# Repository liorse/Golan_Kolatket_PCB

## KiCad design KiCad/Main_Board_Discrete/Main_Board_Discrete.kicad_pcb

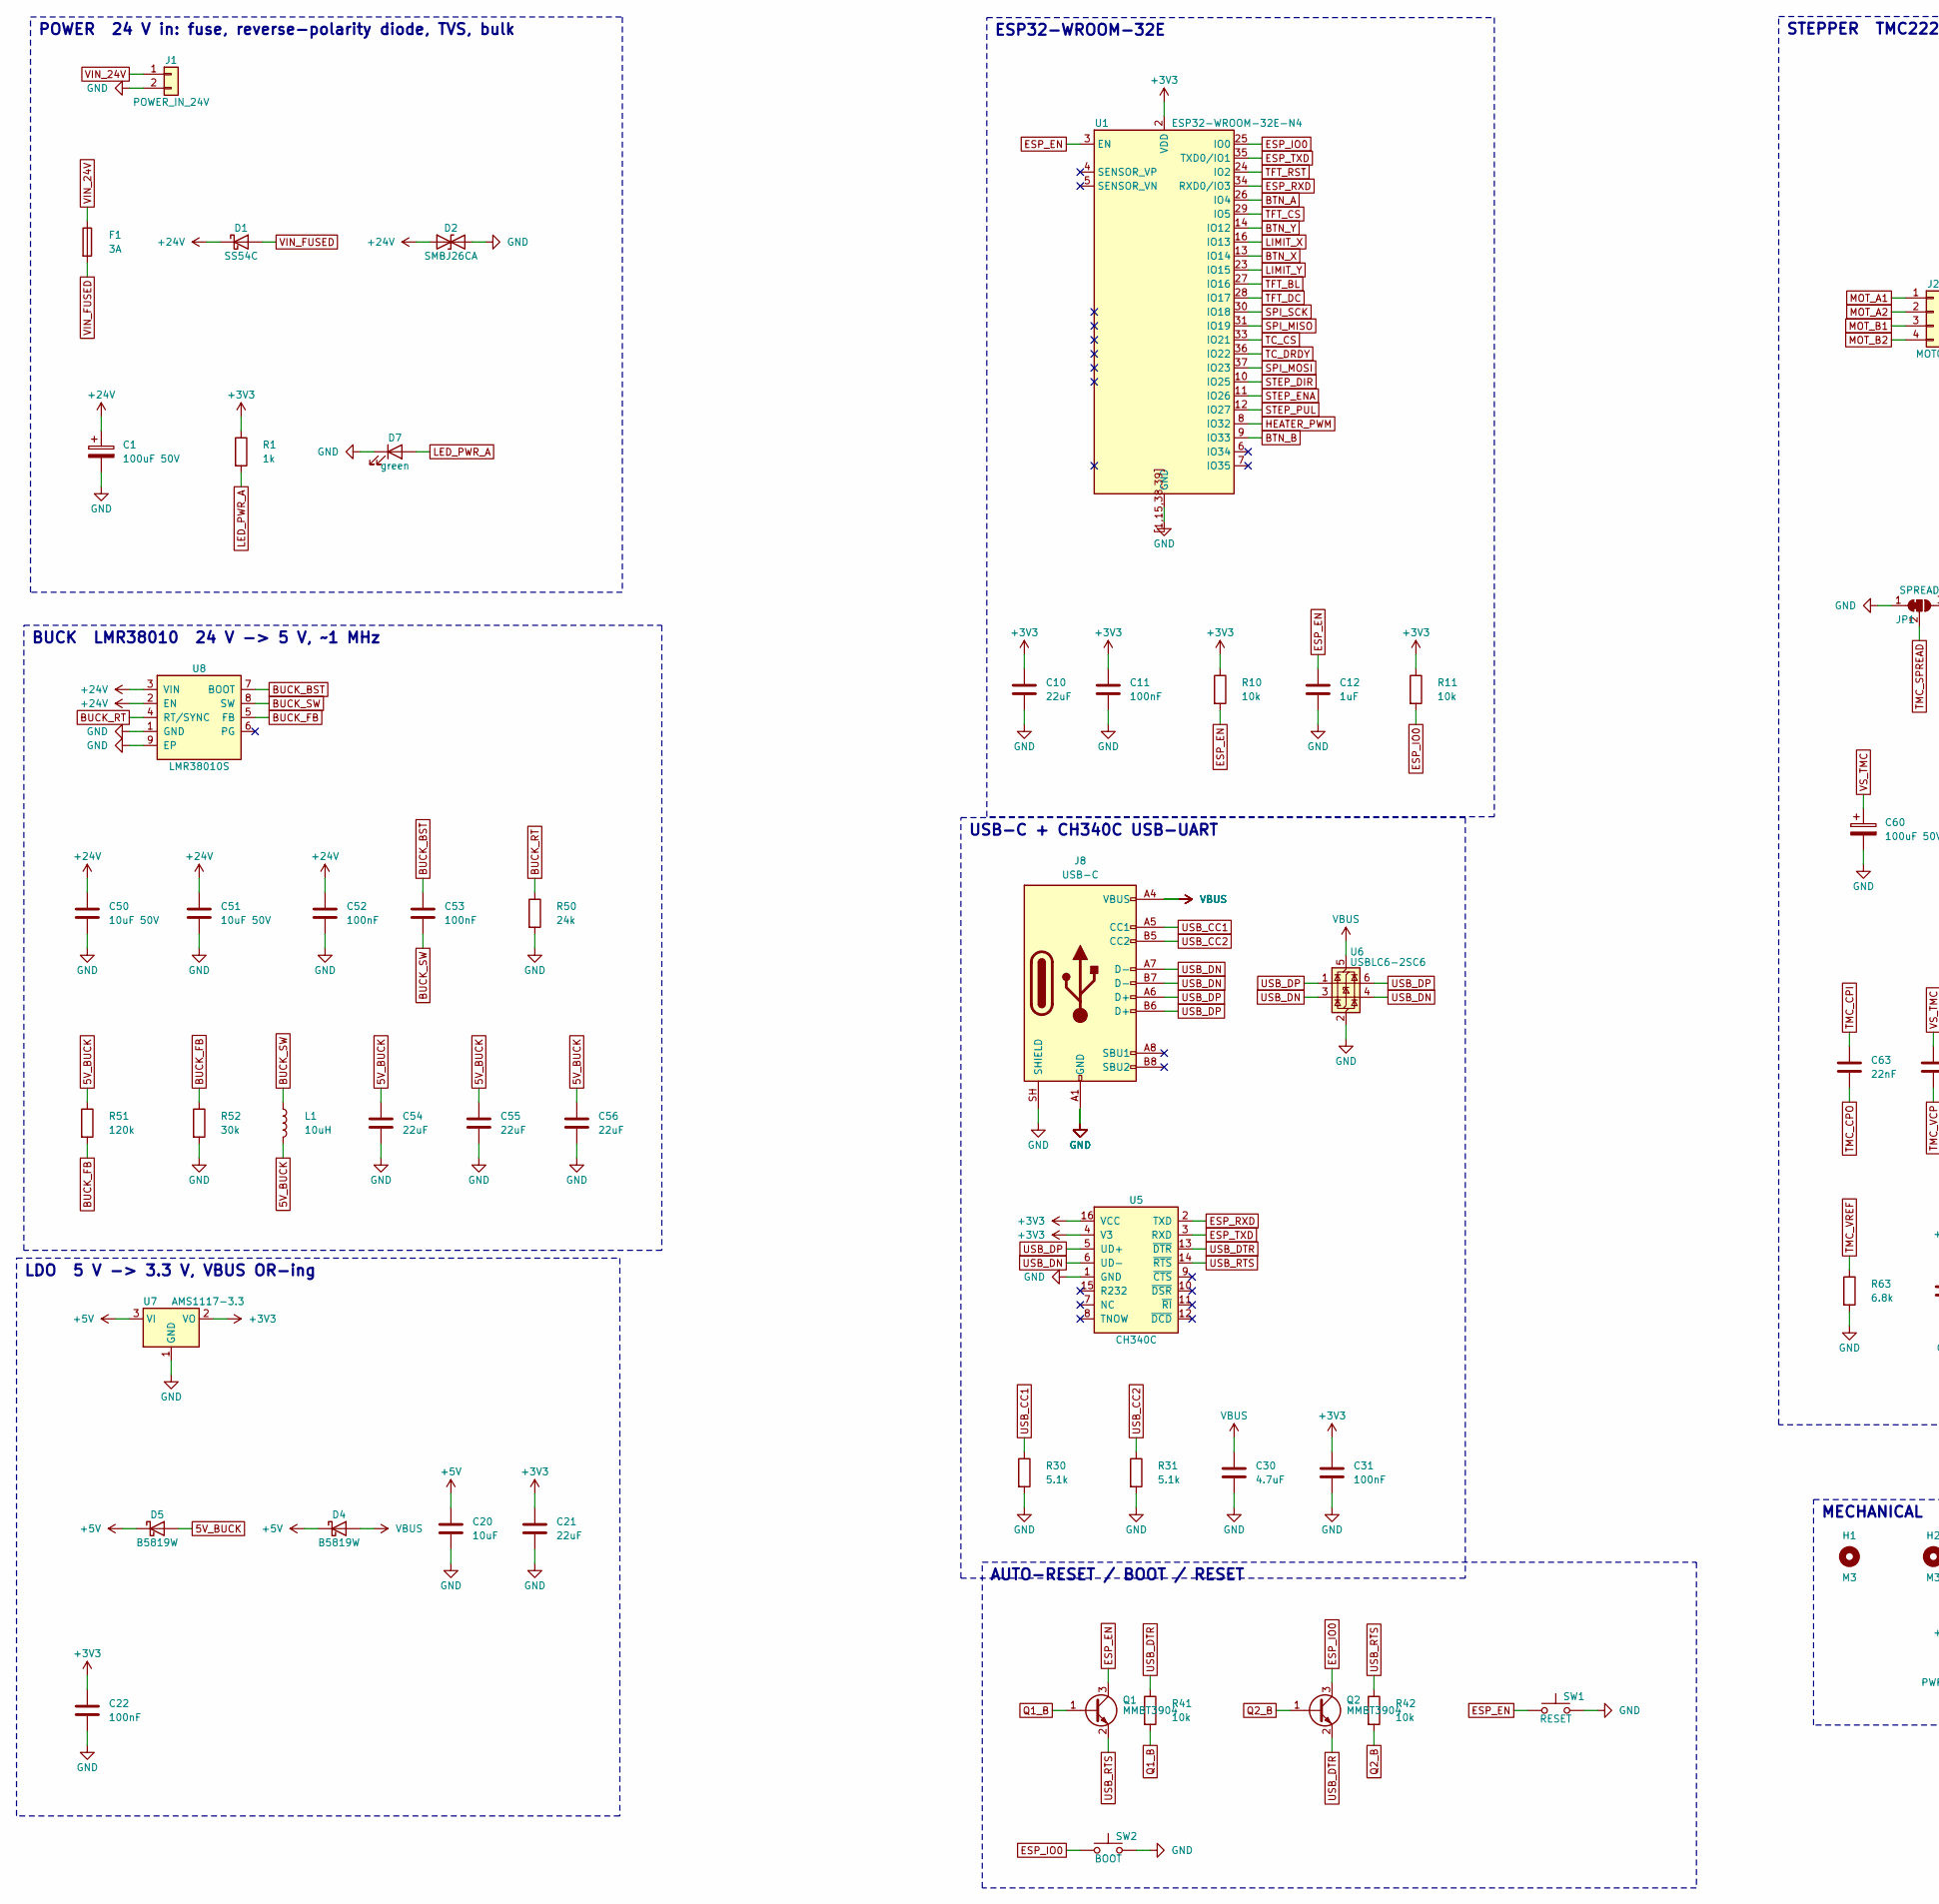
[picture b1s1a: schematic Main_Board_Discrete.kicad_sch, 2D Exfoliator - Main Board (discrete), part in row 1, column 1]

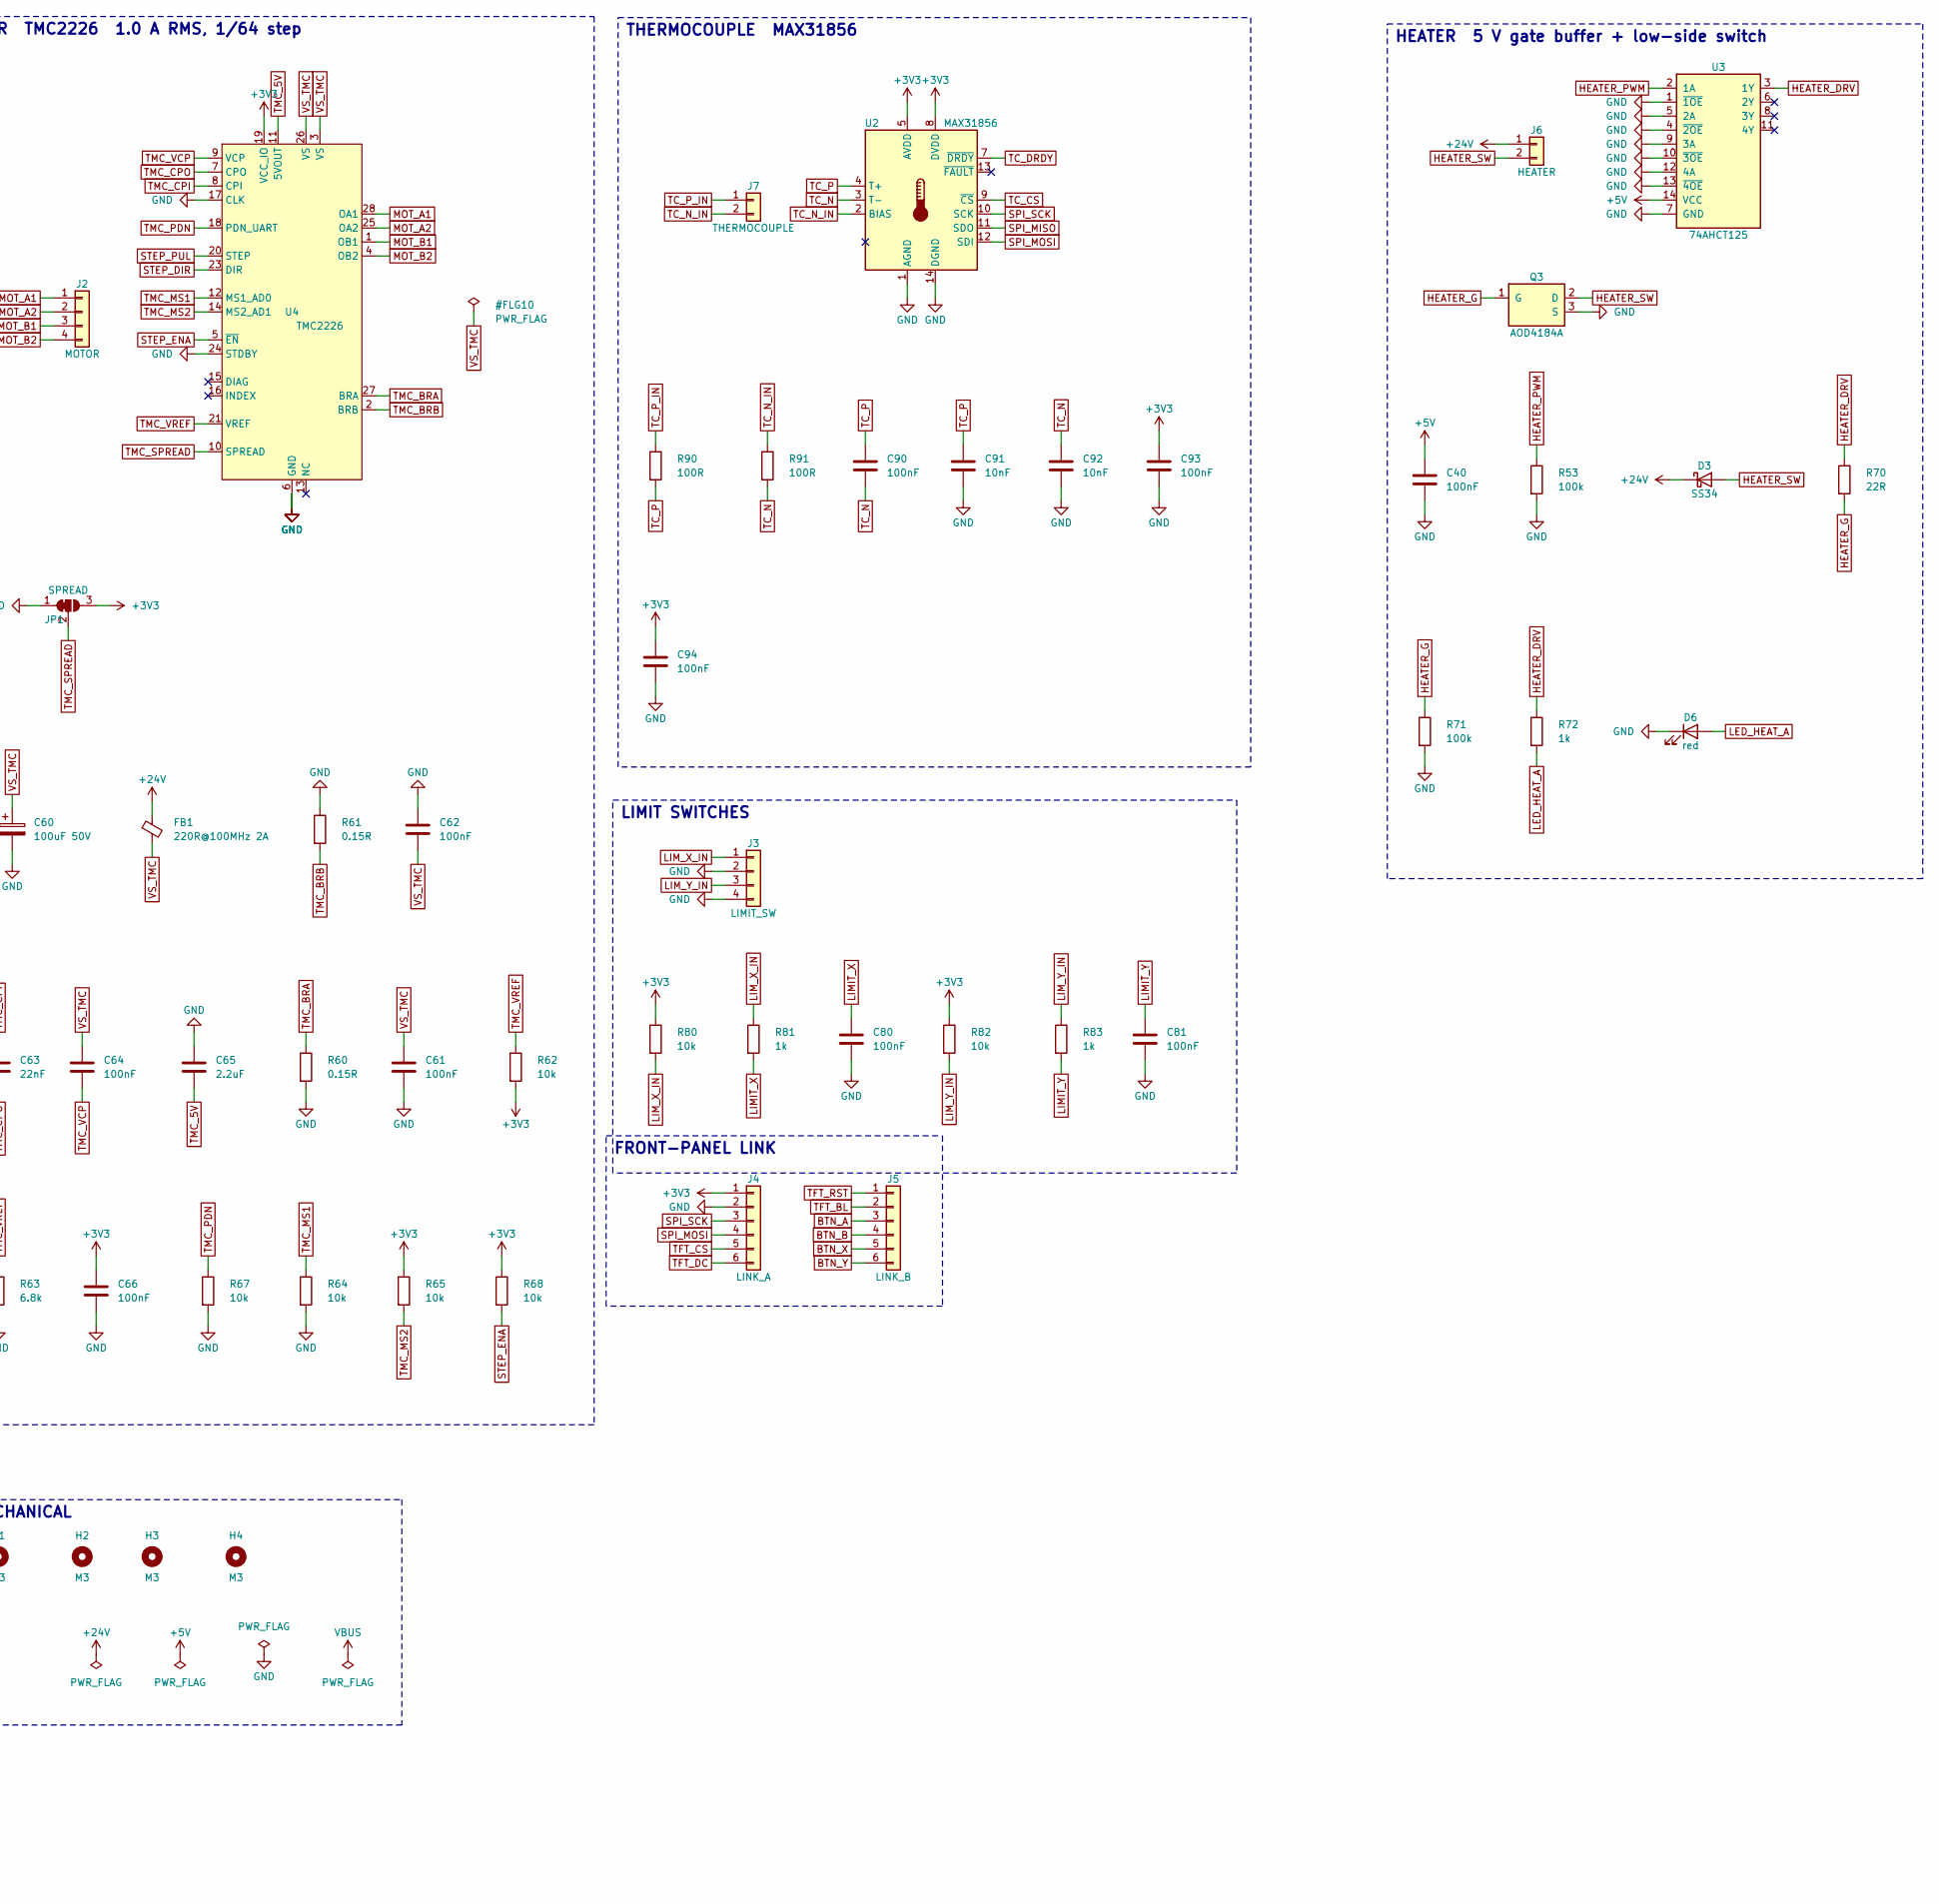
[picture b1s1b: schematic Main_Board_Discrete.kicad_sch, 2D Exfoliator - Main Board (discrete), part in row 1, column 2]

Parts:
C1, C60: 100uF 50V; CP_Elec_8x10; LCSC C2836439
C10, C21: 22uF; C_1206_3216Metric; LCSC C12891
C11, C22, C31, C40, C52, C53, C61, C62, C64, C66, C80, C81, C90, C93, C94: 100nF; C_0603_1608Metric; LCSC C14663
C12: 1uF; C_0603_1608Metric; LCSC C15849
C20: 10uF; C_0805_2012Metric; LCSC C15850
C30: 4.7uF; C_0603_1608Metric; LCSC C19666
C50, C51: 10uF 50V; C_1206_3216Metric; LCSC C13585
C54, C55, C56: 22uF; C_0805_2012Metric; LCSC C45783
C63: 22nF; C_0603_1608Metric; LCSC C21122
C65: 2.2uF; C_0603_1608Metric; LCSC C23630
C91, C92: 10nF; C_0603_1608Metric; LCSC C57112
D1: SS54C; D_SMC; MPN SS54C; LCSC C16103
D2: SMBJ26CA; D_SMB; MPN SMBJ26CA; LCSC C83332
D3: SS34; D_SMA; MPN SS34; LCSC C8678
D4, D5: B5819W; D_SOD-123; MPN B5819W; LCSC C8598
D6: red; LED_0603_1608Metric; MPN KT-0603R; LCSC C2286
D7: green; LED_0805_2012Metric; MPN KT-0805G; LCSC C2297
F1: 3A; Fuse_1206_3216Metric; MPN S1206-S-3.0A; LCSC C553930
FB1: 220R@100MHz 2A; L_0805_2012Metric; MPN BLM21PG221SN1D; LCSC C85840
H1, H2, H3, H4: M3; MountingHole_3.2mm_M3
J1: POWER_IN_24V; PhoenixContact_MSTBA_2,5_2-G-5,08_1x02_P5.08mm_Horizontal; MPN 1757242; LCSC C90074
J2: MOTOR; PhoenixContact_MSTBA_2,5_4-G-5,08_1x04_P5.08mm_Horizontal; MPN 1757268; LCSC C90076
J3: LIMIT_SW; PhoenixContact_MSTBA_2,5_4-G-5,08_1x04_P5.08mm_Horizontal; MPN 1757268; LCSC C90076
J4: LINK_A; PhoenixContact_MSTBA_2,5_6-G-5,08_1x06_P5.08mm_Horizontal; MPN 1757284; LCSC C457198
J5: LINK_B; PhoenixContact_MSTBA_2,5_6-G-5,08_1x06_P5.08mm_Horizontal; MPN 1757284; LCSC C457198
J6: HEATER; PhoenixContact_MSTBA_2,5_2-G-5,08_1x02_P5.08mm_Horizontal; MPN 1757242; LCSC C90074
J7: THERMOCOUPLE; PhoenixContact_MSTBA_2,5_2-G-5,08_1x02_P5.08mm_Horizontal; MPN 1757242; LCSC C90074
J8: USB-C; USB_C_Receptacle_HRO_TYPE-C-31-M-12; MPN TYPE-C-31-M-12; LCSC C165948
JP1: SPREAD; SolderJumper-3_P1.3mm_Bridged12_RoundedPad1.0x1.5mm_NumberL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
L1: 10uH; L_Sunlord_SWPA5040S; MPN SWPA5040S100MT; LCSC C84608
Q1, Q2: MMBT3904; SOT-23; MPN MMBT3904; LCSC C20526
Q3: AOD4184A; TO-252-2; MPN AOD4184A; LCSC C99124
R1, R72, R81, R83: 1k; R_0603_1608Metric; LCSC C21190
R10, R11, R41, R42, R62, R64, R65, R67, R68, R80, R82: 10k; R_0603_1608Metric; LCSC C25804
R30, R31: 5.1k; R_0603_1608Metric; LCSC C23186
R50: 24k; R_0603_1608Metric; LCSC C23352
R51: 120k; R_0603_1608Metric; LCSC C25808
R52: 30k; R_0603_1608Metric; LCSC C22984
R53, R71: 100k; R_0603_1608Metric; LCSC C25803
R60, R61: 0.15R; R_1206_3216Metric; LCSC C858778
R63: 6.8k; R_0603_1608Metric; LCSC C23212
R70: 22R; R_0603_1608Metric; LCSC C23345
R90, R91: 100R; R_0603_1608Metric; LCSC C22775
SW1: RESET; SW_SPST_TL3342; MPN TS-1187A-B-A-B; LCSC C318884
SW2: BOOT; SW_SPST_TL3342; MPN TS-1187A-B-A-B; LCSC C318884
U1: ESP32-WROOM-32E-N4; ESP32-WROOM-32E_Via0.3; MPN ESP32-WROOM-32E-N4; LCSC C701341
U2: MAX31856; TSSOP-14_4.4x5mm_P0.65mm; MPN MAX31856MUD+; LCSC C116632
U3: 74AHCT125; SOIC-14_3.9x8.7mm_P1.27mm; MPN SN74AHCT125DR; LCSC C155176
U4: TMC2226; HTSSOP-28-1EP_4.4x9.7mm_P0.65mm_EP2.75x6.2mm_ThermalVias; MPN TMC2226-SA-T; LCSC C705366
U5: CH340C; SOIC-16_3.9x9.9mm_P1.27mm; MPN CH340C; LCSC C84681
U6: USBLC6-2SC6; SOT-23-6; MPN USBLC6-2SC6; LCSC C7519
U7: AMS1117-3.3; SOT-223-3_TabPin2; MPN AMS1117-3.3; LCSC C6186
U8: LMR38010S; TI_SO-PowerPAD-8_ThermalVias; MPN LMR38010SDDAR; LCSC C5219310

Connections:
5V_BUCK: C54.1, C55.1, C56.1, D5.2 (A), L1.2, R51.1
+3V3: C10.1, C11.1, C21.1, C22.1, C31.1, C66.1, C93.1, C94.1, J4.1, JP1.3 (B), R1.1, R10.1, R11.1, R62.2, R65.1, R68.1, R80.1, R82.1, U1.2 (VDD), U2.5 (AVDD), U2.8 (DVDD), U4.19 (VCC_IO), U5.4 (V3), U5.16 (VCC), U7.2 (VO)
+5V: C20.1, C40.1, D4.1 (K), D5.1 (K), U3.14 (VCC), U7.3 (VI)
+24V: C1.1, C50.1, C51.1, C52.1, D1.1 (K), D2.1 (A1), D3.1 (K), FB1.1, J6.1, U8.2 (EN), U8.3 (VIN)
BTN_A: J5.3, U1.26 (IO4)
BTN_B: J5.4, U1.9 (IO33)
BTN_X: J5.5, U1.13 (IO14)
BTN_Y: J5.6, U1.14 (IO12)
BUCK_BST: C53.1, U8.7 (BOOT)
BUCK_FB: R51.2, R52.1, U8.5 (FB)
BUCK_RT: R50.1, U8.4 (RT/SYNC)
BUCK_SW: C53.2, L1.1, U8.8 (SW)
ESP_EN: C12.1, Q1.3 (C), R10.2, SW1.1, U1.3 (EN)
ESP_IO0: Q2.3 (C), R11.2, SW2.1, U1.25 (IO0)
ESP_RXD: U1.34 (RXD0/IO3), U5.2 (TXD)
ESP_TXD: U1.35 (TXD0/IO1), U5.3 (RXD)
GND: C1.2, C10.2, C11.2, C12.2, C20.2, C21.2, C22.2, C30.2, C31.2, C40.2, C50.2, C51.2, C52.2, C54.2, C55.2, C56.2, C60.2, C61.2, C62.1, C65.1, C66.2, C80.2, C81.2, C91.2, C92.2, C93.2, C94.2, D2.2 (A2), D6.1 (K), D7.1 (K), J1.2, J3.2, J3.4, J4.2, J8.A1 (GND), J8.A12 (GND), J8.B1 (GND), J8.B12 (GND), J8.SH (SHIELD), JP1.1 (A), Q3.3 (S), R30.2, R31.2, R50.2, R52.2, R53.2, R60.2, R61.1, R63.2, R64.2, R67.2, R71.2, SW1.2, SW2.2, U1.1, U1.15, U1.38, U1.39, U1.[1,15,38,39] (GND), U2.1 (AGND), U2.14 (DGND), U3.1 (~1OE), U3.4 (~2OE), U3.5 (2A), U3.7 (GND), U3.9 (3A), U3.10 (~3OE), U3.12 (4A), U3.13 (~4OE), U4.6 (GND), U4.17 (CLK), U4.22 (GND), U4.24 (STDBY), U4.29 (GND), U5.1 (GND), U6.2 (GND), U7.1 (GND), U8.1 (GND), U8.9 (EP)
HEATER_DRV: R70.1, R72.1, U3.3 (1Y)
HEATER_G: Q3.1 (G), R70.2, R71.1
HEATER_PWM: R53.1, U1.8 (IO32), U3.2 (1A)
HEATER_SW: D3.2 (A), J6.2, Q3.2 (D)
LED_HEAT_A: D6.2 (A), R72.2
LED_PWR_A: D7.2 (A), R1.2
LIMIT_X: C80.1, R81.2, U1.16 (IO13)
LIMIT_Y: C81.1, R83.2, U1.23 (IO15)
LIM_X_IN: J3.1, R80.2, R81.1
LIM_Y_IN: J3.3, R82.2, R83.1
MOT_A1: J2.1, U4.28 (OA1)
MOT_A2: J2.2, U4.25 (OA2)
MOT_B1: J2.3, U4.1 (OB1)
MOT_B2: J2.4, U4.4 (OB2)
Q1_B: Q1.1 (B), R41.2
Q2_B: Q2.1 (B), R42.2
SPI_MISO: U1.31 (IO19), U2.11 (SDO)
SPI_MOSI: J4.4, U1.37 (IO23), U2.12 (SDI)
SPI_SCK: J4.3, U1.30 (IO18), U2.10 (SCK)
STEP_DIR: U1.10 (IO25), U4.23 (DIR)
STEP_ENA: R68.2, U1.11 (IO26), U4.5 (~EN)
STEP_PUL: U1.12 (IO27), U4.20 (STEP)
TC_CS: U1.33 (IO21), U2.9 (~CS)
TC_DRDY: U1.36 (IO22), U2.7 (~DRDY)
TC_N: C90.2, C92.1, R91.2, U2.3 (T-)
TC_N_IN: J7.2, R91.1, U2.2 (BIAS)
TC_P: C90.1, C91.1, R90.2, U2.4 (T+)
TC_P_IN: J7.1, R90.1
TFT_BL: J5.2, U1.27 (IO16)
TFT_CS: J4.5, U1.29 (IO5)
TFT_DC: J4.6, U1.28 (IO17)
TFT_RST: J5.1, U1.24 (IO2)
TMC_5V: C65.2, U4.11 (5VOUT)
TMC_BRA: R60.1, U4.27 (BRA)
TMC_BRB: R61.2, U4.2 (BRB)
TMC_CPI: C63.1, U4.8 (CPI)
TMC_CPO: C63.2, U4.7 (CPO)
TMC_MS1: R64.1, U4.12 (MS1_AD0)
TMC_MS2: R65.2, U4.14 (MS2_AD1)
TMC_PDN: R67.1, U4.18 (PDN_UART)
TMC_SPREAD: JP1.2 (C), U4.10 (SPREAD)
TMC_VCP: C64.2, U4.9 (VCP)
TMC_VREF: R62.1, R63.1, U4.21 (VREF)
USB_CC1: J8.A5 (CC1), R30.1
USB_CC2: J8.B5 (CC2), R31.1
USB_DN: J8.A7 (D-), J8.B7 (D-), U5.6 (UD-), U6.3 (I/O2), U6.4 (I/O2)
USB_DP: J8.A6 (D+), J8.B6 (D+), U5.5 (UD+), U6.1 (I/O1), U6.6 (I/O1)
USB_DTR: Q2.2 (E), R41.1, U5.13 (~DTR)
USB_RTS: Q1.2 (E), R42.1, U5.14 (~RTS)
VBUS: C30.1, D4.2 (A), J8.A4 (VBUS), J8.A9 (VBUS), J8.B4 (VBUS), J8.B9 (VBUS), U6.5 (VBUS)
VIN_24V: F1.1, J1.1
VIN_FUSED: D1.2 (A), F1.2
VS_TMC: C60.1, C61.1, C62.2, C64.1, FB1.2, U4.3 (VS), U4.26 (VS)

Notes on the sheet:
POWER 24 V in: fuse, reverse-polarity diode, TVS, bulk
STEPPER TMC2226 1.0 A RMS, 1/64 step
LIMIT SWITCHES
HEATER 5 V gate buffer + low-side switch
FRONT-PANEL LINK
THERMOCOUPLE MAX31856
MECHANICAL
BUCK LMR38010 24 V -> 5 V, ~1 MHz
LDO 5 V -> 3.3 V, VBUS OR-ing
USB-C + CH340C USB-UART
AUTO-RESET / BOOT / RESET
ESP32-WROOM-32E

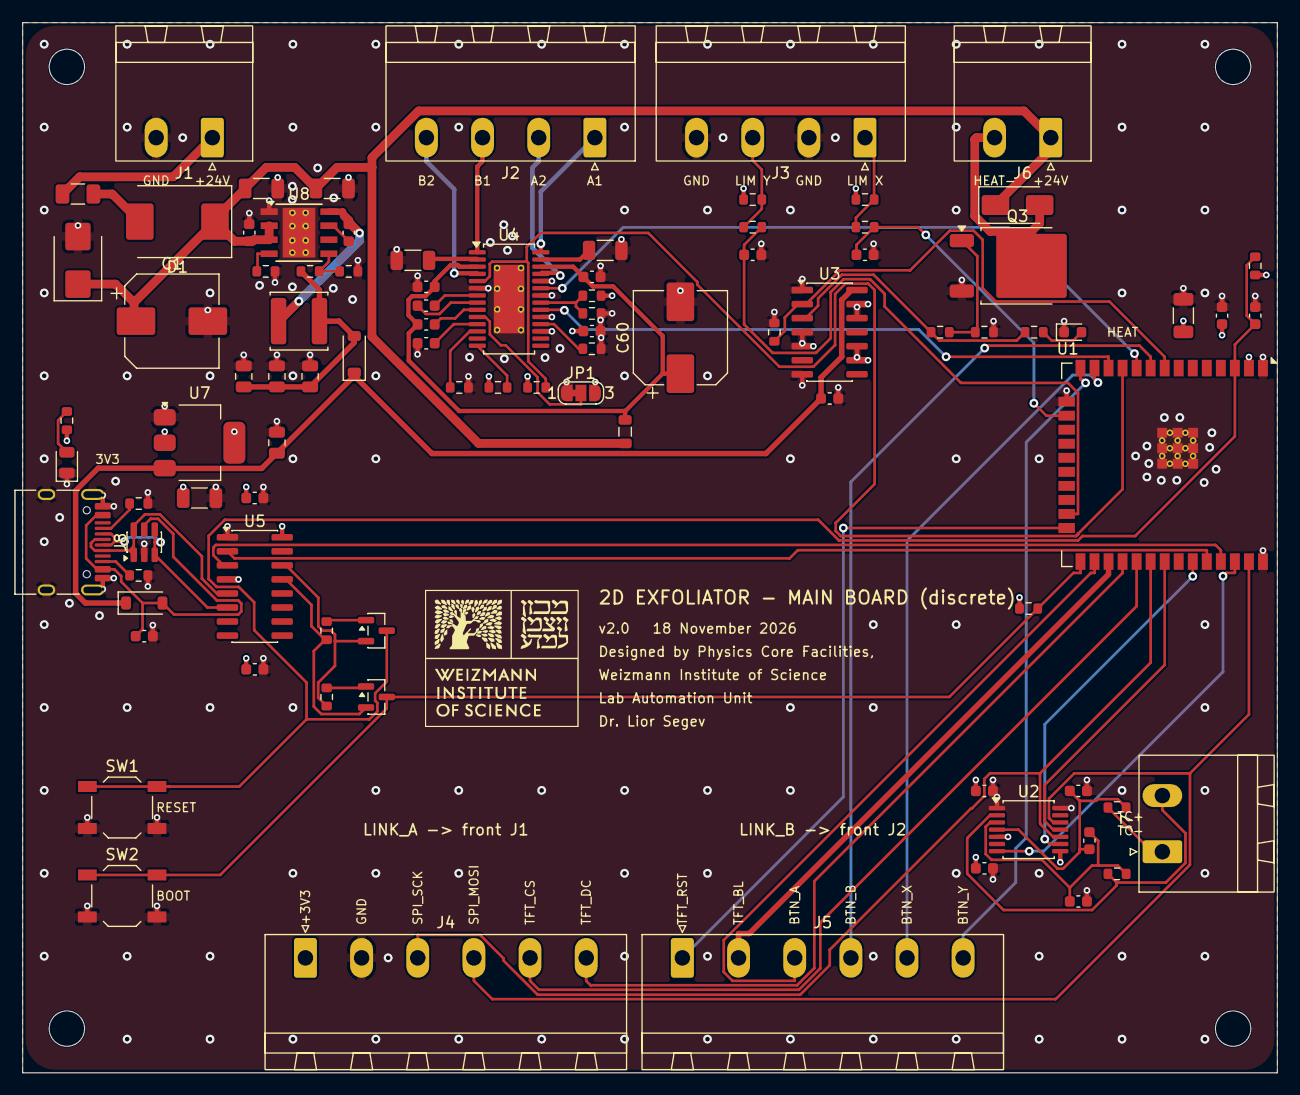
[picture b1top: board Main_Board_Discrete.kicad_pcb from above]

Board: 4 copper layers, 113.5 x 95.0 mm, 95 parts (0 on the bottom side), 70 nets.

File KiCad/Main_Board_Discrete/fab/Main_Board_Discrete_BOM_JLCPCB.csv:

Comment,Designator,Footprint,LCSC Part #,MPN,Qty,Mount
100uF 50V,"C1,C60",CP_Elec_8x10,C2836439,,2,SMD
22uF,"C10,C21",C_1206_3216Metric,C12891,,2,SMD
100nF,"C11,C22,C31,C40,C52,C53,C61,C62,C64,C66,C80,C81,C90,C93,C94",C_0603_1608Metric,C14663,,15,SMD
1uF,C12,C_0603_1608Metric,C15849,,1,SMD
10uF,C20,C_0805_2012Metric,C15850,,1,SMD
4.7uF,C30,C_0603_1608Metric,C19666,,1,SMD
10uF 50V,"C50,C51",C_1206_3216Metric,C13585,,2,SMD
22uF,"C54,C55,C56",C_0805_2012Metric,C45783,,3,SMD
22nF,C63,C_0603_1608Metric,C21122,,1,SMD
2.2uF,C65,C_0603_1608Metric,C23630,,1,SMD
10nF,"C91,C92",C_0603_1608Metric,C57112,,2,SMD
SS54C,D1,D_SMC,C16103,SS54C,1,SMD
SMBJ26CA,D2,D_SMB,C83332,SMBJ26CA,1,SMD
SS34,D3,D_SMA,C8678,SS34,1,SMD
B5819W,"D4,D5",D_SOD-123,C8598,B5819W,2,SMD
red,D6,LED_0603_1608Metric,C2286,KT-0603R,1,SMD
green,D7,LED_0805_2012Metric,C2297,KT-0805G,1,SMD
3A,F1,Fuse_1206_3216Metric,C553930,S1206-S-3.0A,1,SMD
220R@100MHz 2A,FB1,L_0805_2012Metric,C85840,BLM21PG221SN1D,1,SMD
POWER_IN_24V/HEATER/THERMOCOUPLE,"J1,J6,J7","PhoenixContact_MSTBA_2,5_2-G-5,08_1x02_P5.08mm_Horizontal",C90074,1757242,3,THT
MOTOR/LIMIT_SW,"J2,J3","PhoenixContact_MSTBA_2,5_4-G-5,08_1x04_P5.08mm_Horizontal",C90076,1757268,2,THT
LINK_A/LINK_B,"J4,J5","PhoenixContact_MSTBA_2,5_6-G-5,08_1x06_P5.08mm_Horizontal",C457198,1757284,2,THT
USB-C,J8,USB_C_Receptacle_HRO_TYPE-C-31-M-12,C165948,TYPE-C-31-M-12,1,THT
10uH,L1,L_Sunlord_SWPA5040S,C84608,SWPA5040S100MT,1,SMD
MMBT3904,"Q1,Q2",SOT-23,C20526,MMBT3904,2,SMD
AOD4184A,Q3,TO-252-2,C99124,AOD4184A,1,SMD
1k,"R1,R72,R81,R83",R_0603_1608Metric,C21190,,4,SMD
10k,"R10,R11,R41,R42,R62,R64,R65,R67,R68,R80,R82",R_0603_1608Metric,C25804,,11,SMD
5.1k,"R30,R31",R_0603_1608Metric,C23186,,2,SMD
24k,R50,R_0603_1608Metric,C23352,,1,SMD
120k,R51,R_0603_1608Metric,C25808,,1,SMD
30k,R52,R_0603_1608Metric,C22984,,1,SMD
100k,"R53,R71",R_0603_1608Metric,C25803,,2,SMD
0.15R,"R60,R61",R_1206_3216Metric,C858778,,2,SMD
6.8k,R63,R_0603_1608Metric,C23212,,1,SMD
22R,R70,R_0603_1608Metric,C23345,,1,SMD
100R,"R90,R91",R_0603_1608Metric,C22775,,2,SMD
RESET/BOOT,"SW1,SW2",SW_SPST_TL3342,C318884,TS-1187A-B-A-B,2,SMD
ESP32-WROOM-32E-N4,U1,ESP32-WROOM-32E_Via0.3,C701341,ESP32-WROOM-32E-N4,1,THT
MAX31856,U2,TSSOP-14_4.4x5mm_P0.65mm,C116632,MAX31856MUD+,1,SMD
74AHCT125,U3,SOIC-14_3.9x8.7mm_P1.27mm,C155176,SN74AHCT125DR,1,SMD
TMC2226,U4,HTSSOP-28-1EP_4.4x9.7mm_P0.65mm_EP2.75x6.2mm_ThermalVias,C705366,TMC2226-SA-T,1,THT
CH340C,U5,SOIC-16_3.9x9.9mm_P1.27mm,C84681,CH340C,1,SMD
USBLC6-2SC6,U6,SOT-23-6,C7519,USBLC6-2SC6,1,SMD
AMS1117-3.3,U7,SOT-223-3_TabPin2,C6186,AMS1117-3.3,1,SMD
LMR38010S,U8,TI_SO-PowerPAD-8_ThermalVias,C5219310,LMR38010SDDAR,1,THT

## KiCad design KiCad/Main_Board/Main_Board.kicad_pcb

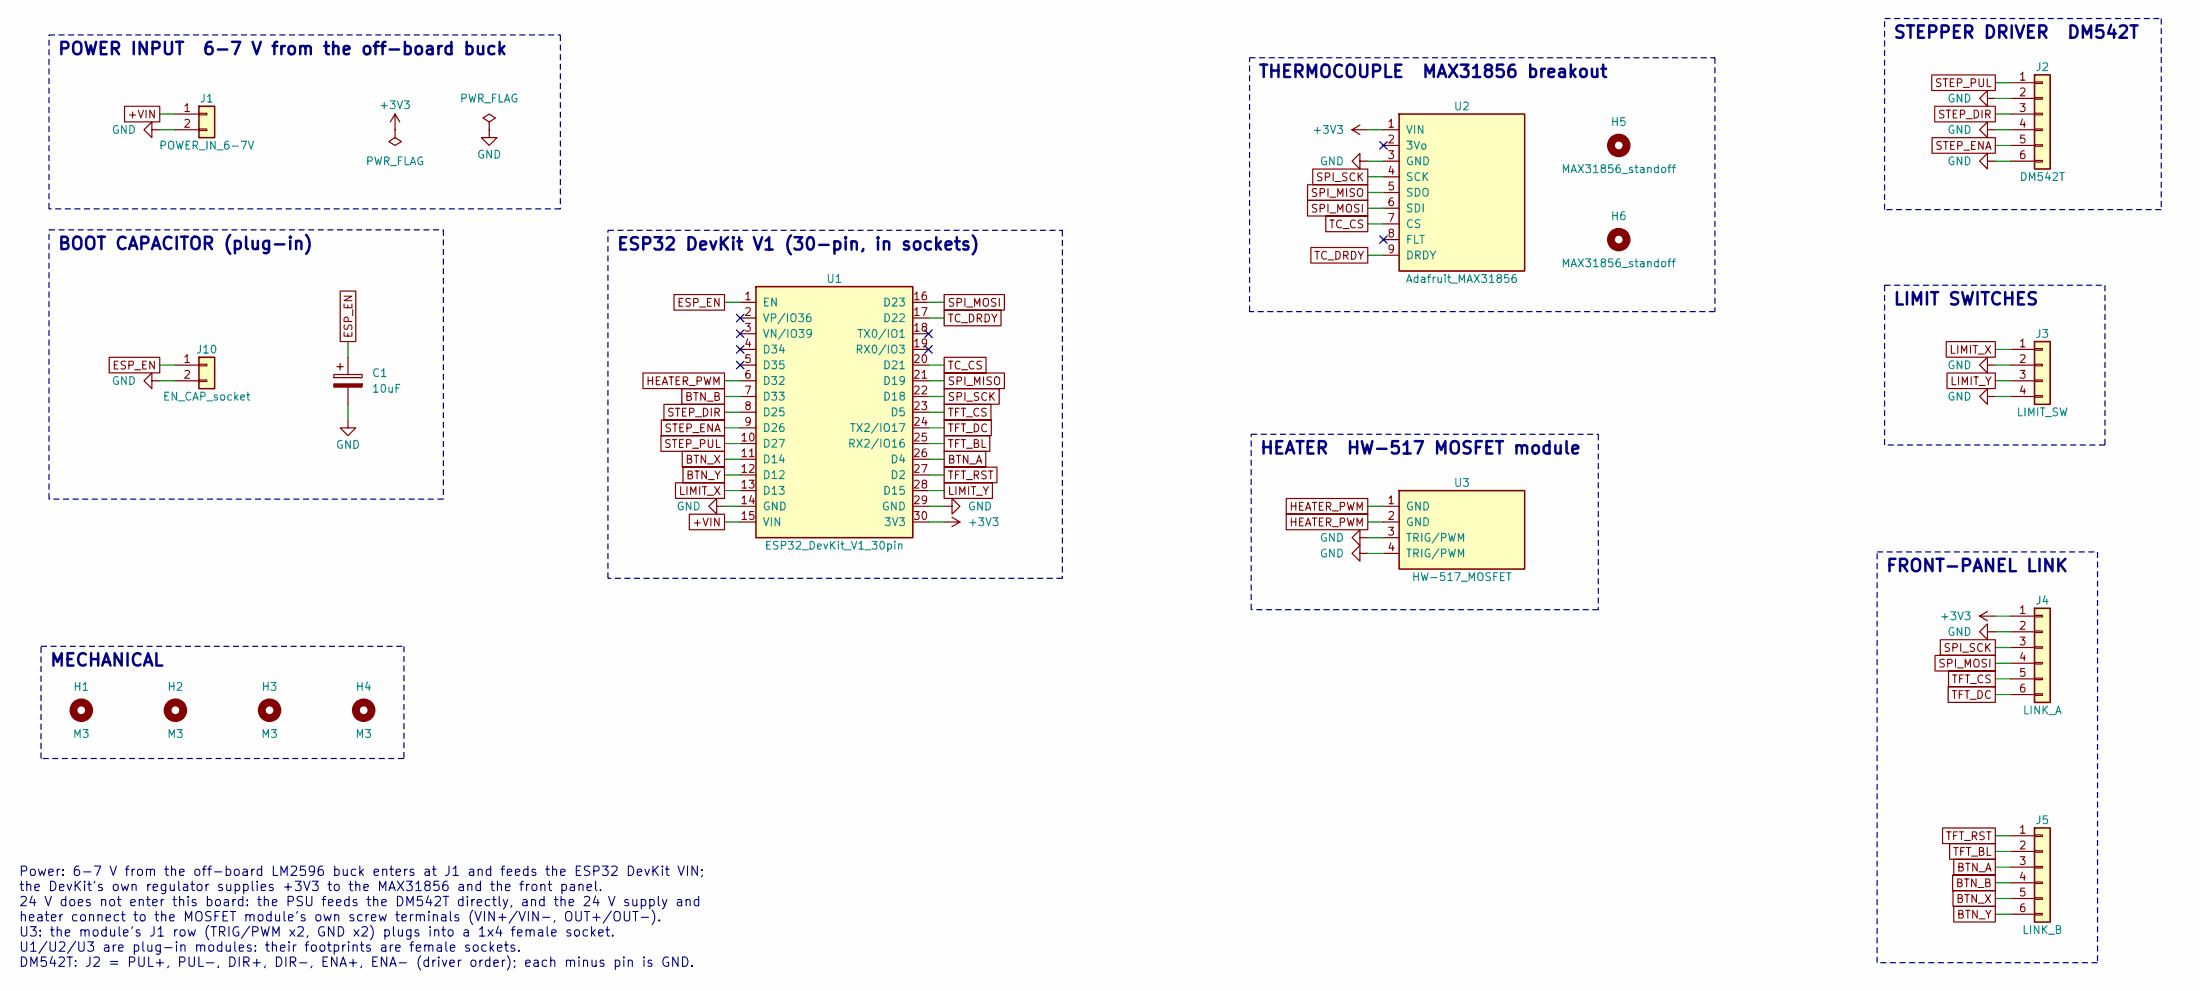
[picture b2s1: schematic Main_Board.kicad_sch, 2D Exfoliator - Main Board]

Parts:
C1: 10uF
H1, H2, H3, H4: M3; MountingHole_3.2mm_M3
H5, H6: MAX31856_standoff; MountingHole_2.7mm_M2.5
J1: POWER_IN_6-7V; PhoenixContact_MSTBA_2,5_2-G-5,08_1x02_P5.08mm_Horizontal
J2: DM542T; PhoenixContact_MSTBA_2,5_6-G-5,08_1x06_P5.08mm_Horizontal
J3: LIMIT_SW; PhoenixContact_MSTBA_2,5_4-G-5,08_1x04_P5.08mm_Horizontal
J4: LINK_A; PhoenixContact_MSTBA_2,5_6-G-5,08_1x06_P5.08mm_Horizontal
J5: LINK_B; PhoenixContact_MSTBA_2,5_6-G-5,08_1x06_P5.08mm_Horizontal
J10: EN_CAP_socket; PinSocket_1x02_P2.54mm_Vertical
U1: ESP32_DevKit_V1_30pin; ESP32_DevKit_V1_30pin_Socket
U2: Adafruit_MAX31856; PinSocket_1x09_P2.54mm_Vertical
U3: HW-517_MOSFET; PinSocket_1x04_P2.54mm_Vertical

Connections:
+3V3: J4.1, U1.30 (3V3), U2.1 (VIN)
+VIN: J1.1, U1.15 (VIN)
BTN_A: J5.3, U1.26 (D4)
BTN_B: J5.4, U1.7 (D33)
BTN_X: J5.5, U1.11 (D14)
BTN_Y: J5.6, U1.12 (D12)
ESP_EN: C1.1, J10.1, U1.1 (EN)
GND: C1.2, J1.2, J2.2, J2.4, J2.6, J3.2, J3.4, J4.2, J10.2, U1.14 (GND), U1.29 (GND), U2.3 (GND), U3.3 (TRIG/PWM), U3.4 (TRIG/PWM)
HEATER_PWM: U1.6 (D32), U3.1 (GND), U3.2 (GND)
LIMIT_X: J3.1, U1.13 (D13)
LIMIT_Y: J3.3, U1.28 (D15)
SPI_MISO: U1.21 (D19), U2.5 (SDO)
SPI_MOSI: J4.4, U1.16 (D23), U2.6 (SDI)
SPI_SCK: J4.3, U1.22 (D18), U2.4 (SCK)
STEP_DIR: J2.3, U1.8 (D25)
STEP_ENA: J2.5, U1.9 (D26)
STEP_PUL: J2.1, U1.10 (D27)
TC_CS: U1.20 (D21), U2.7 (CS)
TC_DRDY: U1.17 (D22), U2.9 (DRDY)
TFT_BL: J5.2, U1.25 (RX2/IO16)
TFT_CS: J4.5, U1.23 (D5)
TFT_DC: J4.6, U1.24 (TX2/IO17)
TFT_RST: J5.1, U1.27 (D2)

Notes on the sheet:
POWER INPUT 6-7 V from the off-board buck
STEPPER DRIVER DM542T
LIMIT SWITCHES
FRONT-PANEL LINK
ESP32 DevKit V1 (30-pin, in sockets)
THERMOCOUPLE MAX31856 breakout
HEATER HW-517 MOSFET module
BOOT CAPACITOR (plug-in)
MECHANICAL
Power: 6-7 V from the off-board LM2596 buck enters at J1 and feeds the ESP32 DevKit VIN; the DevKit's own regulator supplies +3V3 to the MAX31856 and the front panel. 24 V does not enter this board: the PSU feeds the DM542T directly, and the 24 V supply and heater connect to the MOSFET module's own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

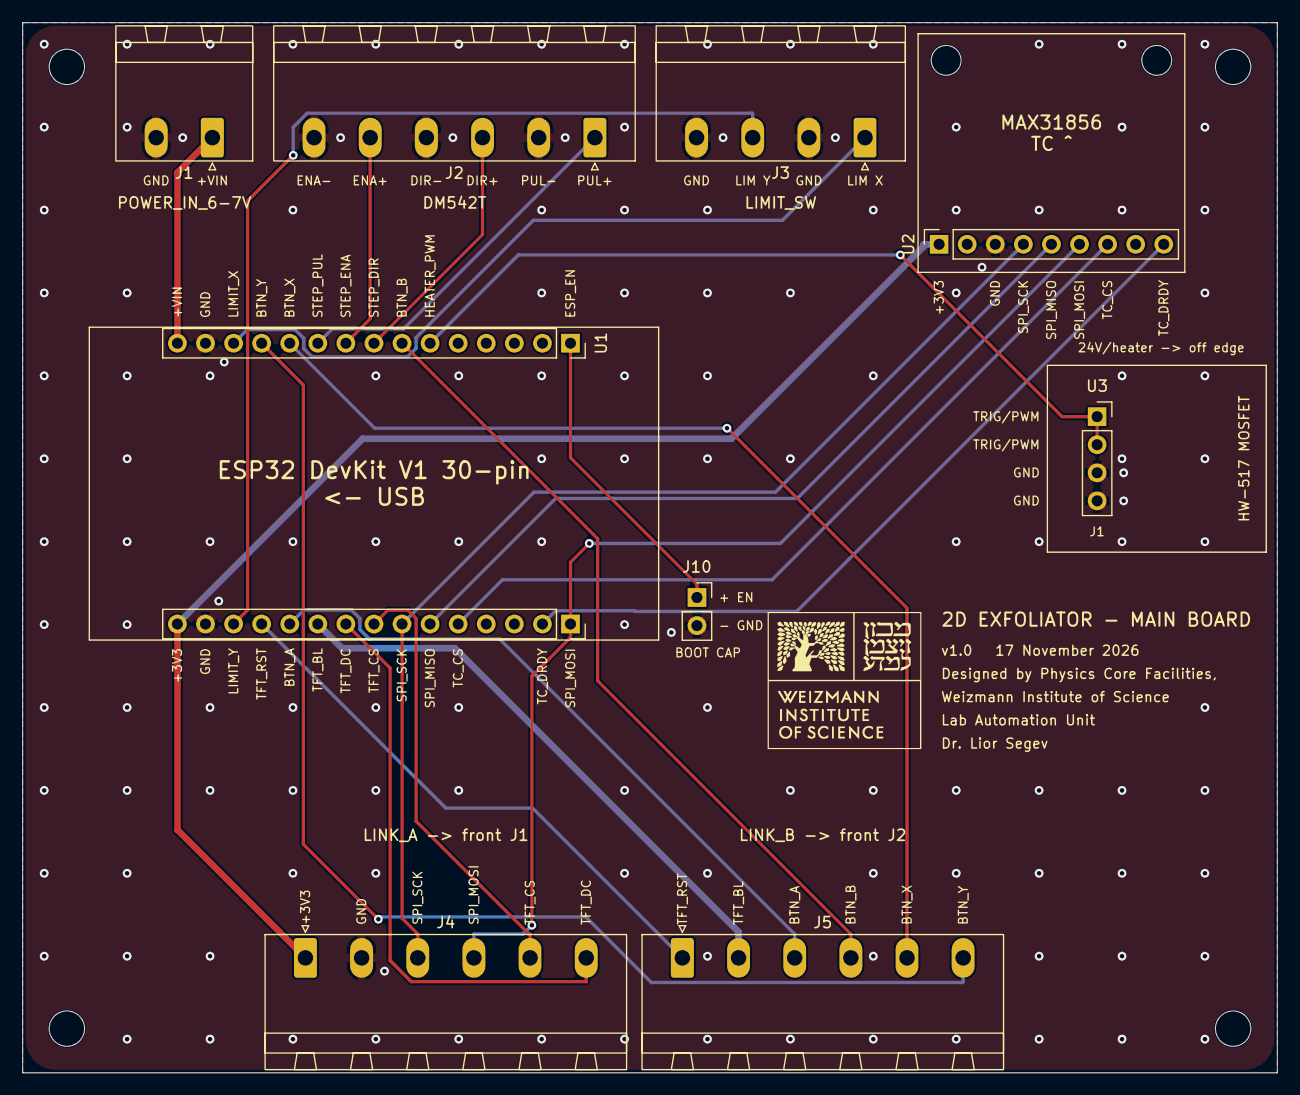
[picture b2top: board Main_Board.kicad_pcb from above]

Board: 2 copper layers, 113.5 x 95.0 mm, 15 parts (0 on the bottom side), 23 nets.

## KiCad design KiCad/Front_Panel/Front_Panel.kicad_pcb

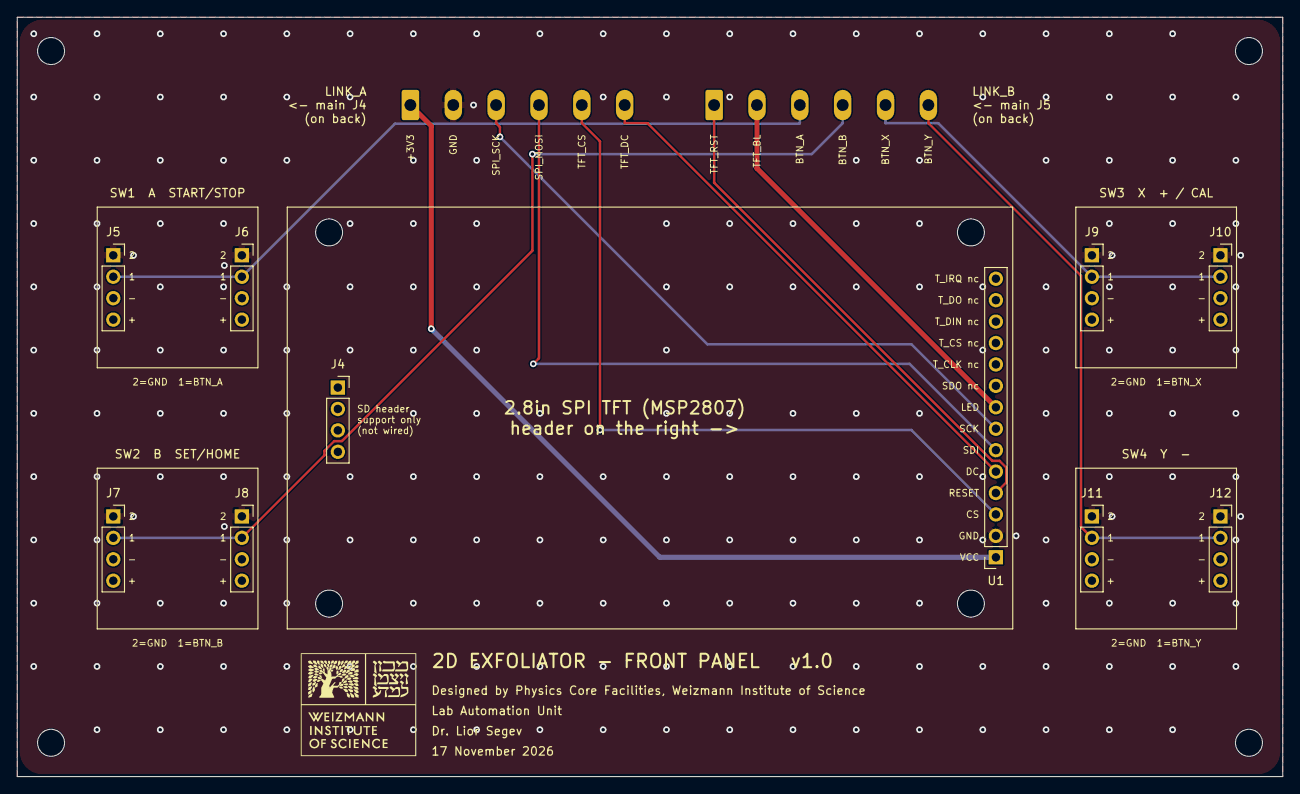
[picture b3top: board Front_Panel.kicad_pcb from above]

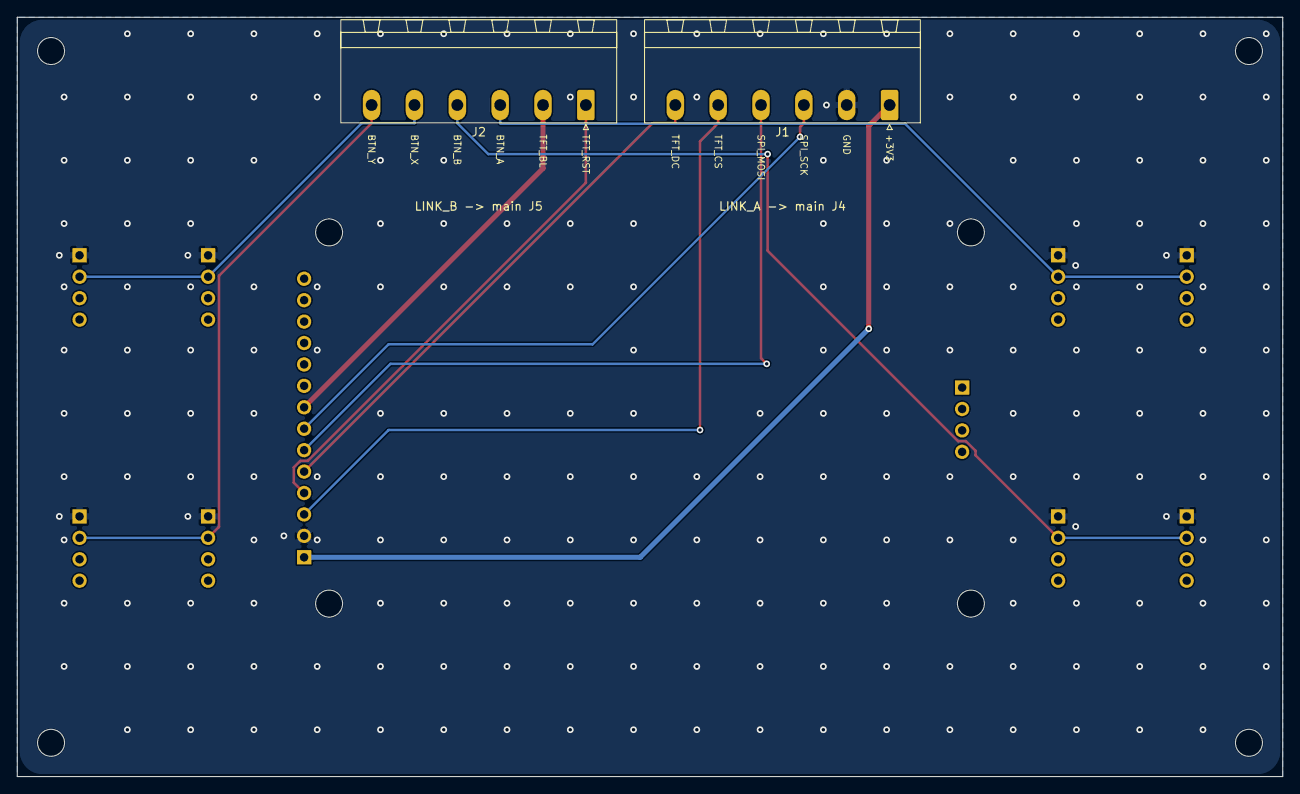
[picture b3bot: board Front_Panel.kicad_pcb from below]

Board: 2 copper layers, 150.0 x 90.0 mm, 20 parts (2 on the bottom side), 12 nets.

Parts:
H1, H2, H3, H4: M3; MountingHole_3.2mm_M3
H5, H6, H7, H8: Display_standoff; MountingHole_3.2mm_M3
J1: LINK_A; PhoenixContact_MSTBA_2,5_6-G-5,08_1x06_P5.08mm_Horizontal
J2: LINK_B; PhoenixContact_MSTBA_2,5_6-G-5,08_1x06_P5.08mm_Horizontal
J4: TFT_SD_support; PinSocket_1x04_P2.54mm_Vertical
J5: SW1_L_socket; PinSocket_1x04_P2.54mm_Vertical
J6: SW1_R_socket; PinSocket_1x04_P2.54mm_Vertical
J7: SW2_L_socket; PinSocket_1x04_P2.54mm_Vertical
J8: SW2_R_socket; PinSocket_1x04_P2.54mm_Vertical
J9: SW3_L_socket; PinSocket_1x04_P2.54mm_Vertical
J10: SW3_R_socket; PinSocket_1x04_P2.54mm_Vertical
J11: SW4_L_socket; PinSocket_1x04_P2.54mm_Vertical
J12: SW4_R_socket; PinSocket_1x04_P2.54mm_Vertical
U1: TFT_2.8in_SPI; PinSocket_1x14_P2.54mm_Vertical

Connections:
+3V3: J1.1, U1.1
BTN_A: J2.3, J5.2, J6.2
BTN_B: J2.4, J7.2, J8.2
BTN_X: J2.5, J9.2, J10.2
BTN_Y: J2.6, J11.2, J12.2
GND: J1.2, J5.1, J6.1, J7.1, J8.1, J9.1, J10.1, J11.1, J12.1, U1.2
SPI_MOSI: J1.4, U1.6
SPI_SCK: J1.3, U1.7
TFT_BL: J2.2, U1.8
TFT_CS: J1.5, U1.3
TFT_DC: J1.6, U1.5
TFT_RST: J2.1, U1.4

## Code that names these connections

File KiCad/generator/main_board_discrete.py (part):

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# ==========================================================================================
# Limit switches: 10k pull-up at the terminal, 1k + 100 nF RC into the GPIO (active-low)
# ==========================================================================================
for ax, (pin_x, raw, gpio) in enumerate(((76.20, "LIM_X_IN", "LIMIT_X"), (66.04, "LIM_Y_IN", "LIMIT_Y"))):
    R("R8%d" % (2 * ax), "10k", "+3V3", raw, (pin_x, 16.0), 0, "lim")
    R("R8%d" % (2 * ax + 1), "1k", raw, gpio, (pin_x, 18.5), 0, "lim")
    C("C8%d" % ax, "100nF", gpio, "GND", (pin_x, 21.0), 0, "lim")
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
